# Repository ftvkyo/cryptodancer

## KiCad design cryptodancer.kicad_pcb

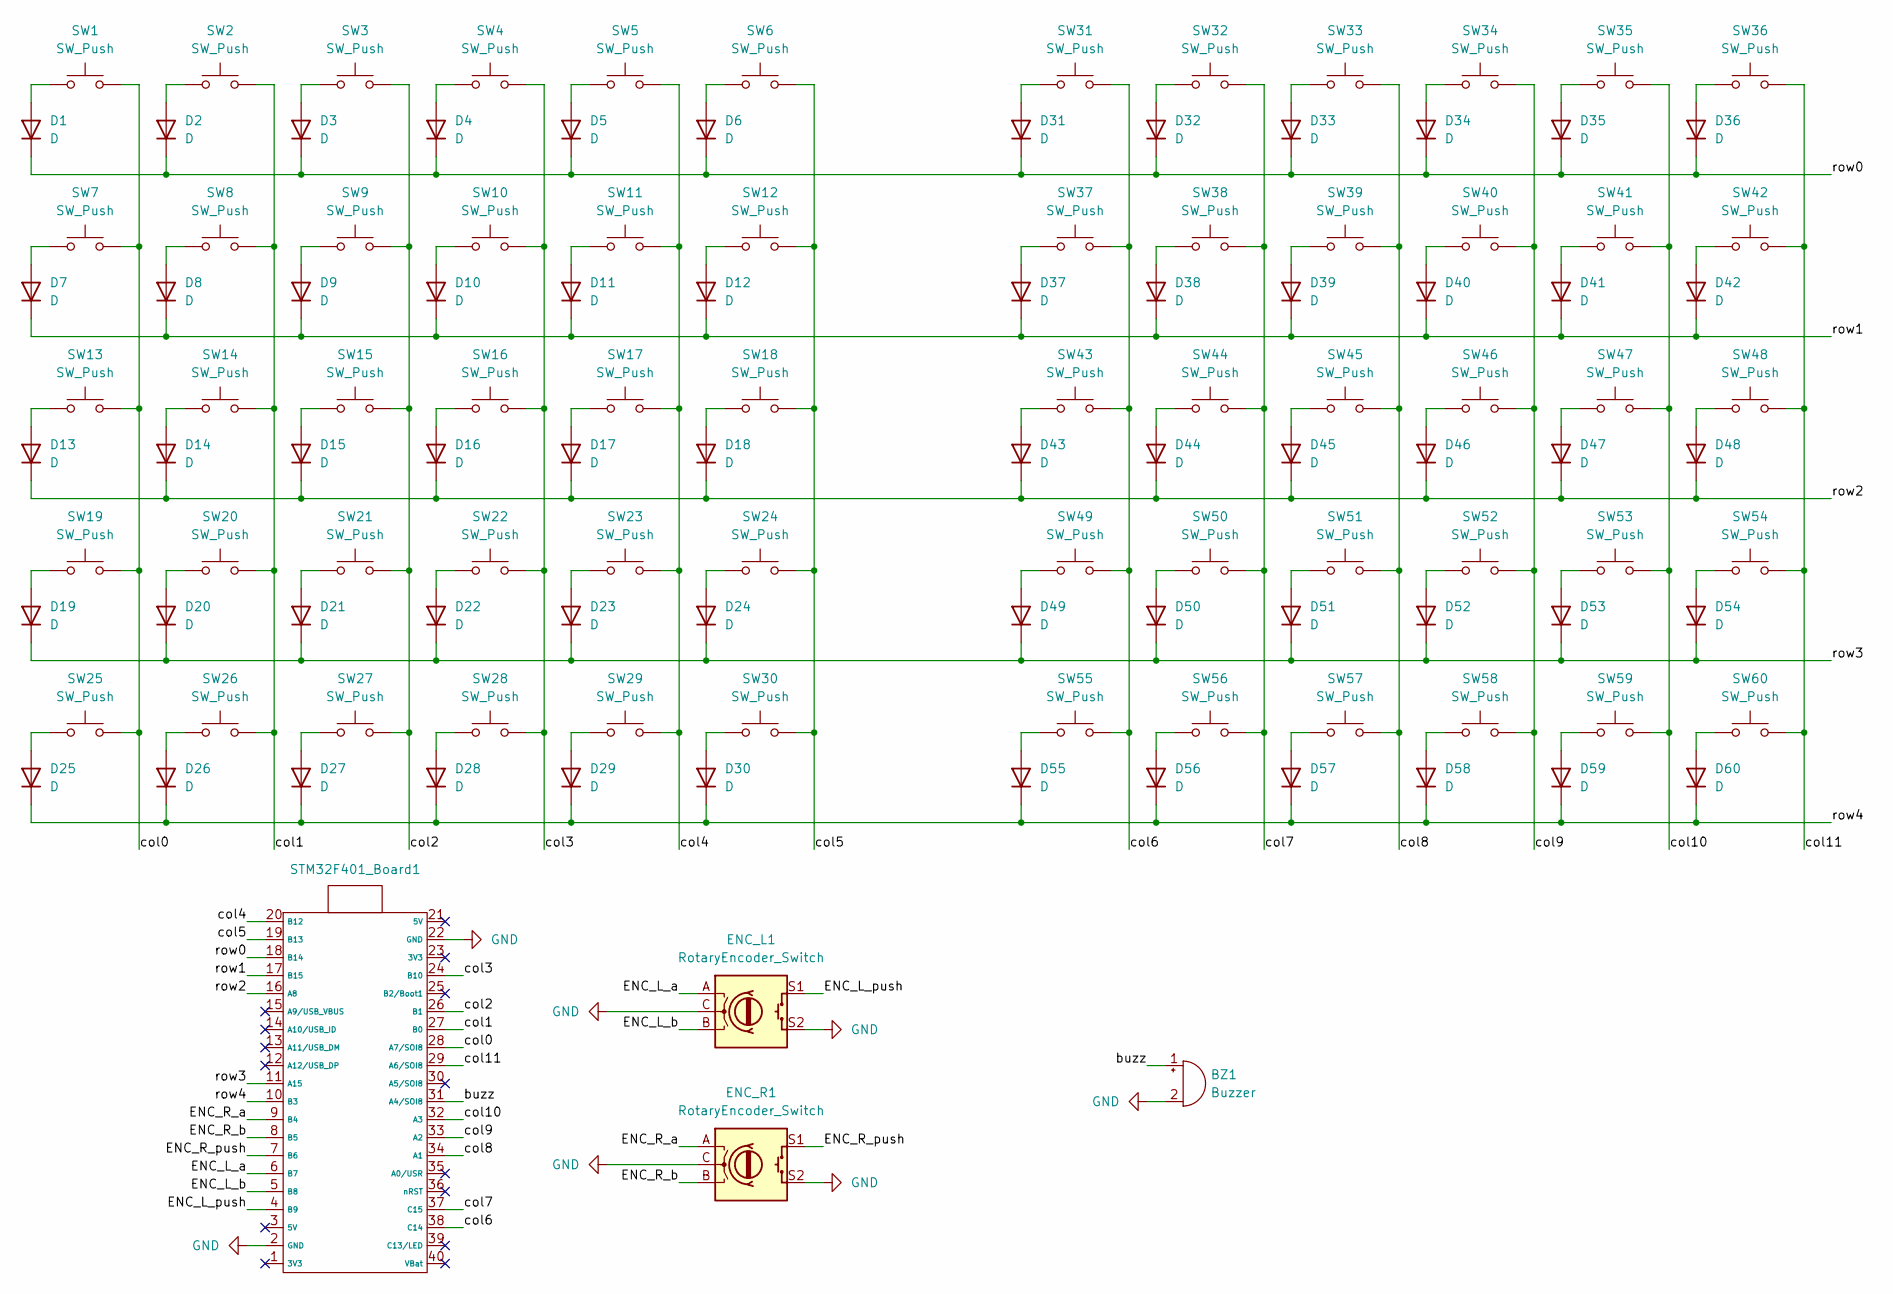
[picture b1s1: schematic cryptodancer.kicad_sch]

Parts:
BZ1: Buzzer; Buzzer_Murata_PKLCS1212E
D1, D2, D3, D4, D5, D6, D7, D8, D9, D10, D11, D12, D13, D14, D15, D16, D17, D18, D19, D20, D21, D22, D23, D24, D25, D26, D27, D28, D29, D30, D31, D32, D33, D34, D35, D36, D37, D38, D39, D40, D41, D42, D43, D44, D45, D46, D47, D48, D49, D50, D51, D52, D53, D54, D55, D56, D57, D58, D59, D60: D; D_1N4148_TH
ENC_L1: RotaryEncoder_Switch; RotaryEncoder_Alps_EC11E-Switch_Vertical_H20mm_MountingHoles
ENC_R1: RotaryEncoder_Switch; RotaryEncoder_Alps_EC11E-Switch_Vertical_H20mm_MountingHoles
STM32F401_Board1: STM32F401_Board
SW1, SW2, SW3, SW4, SW5, SW6, SW7, SW8, SW9, SW10, SW11, SW12, SW13, SW14, SW15, SW16, SW17, SW18, SW19, SW20, SW21, SW22, SW23, SW24, SW25, SW26, SW27, SW28, SW29, SW30, SW31, SW32, SW33, SW34, SW35, SW36, SW37, SW38, SW39, SW40, SW41, SW42, SW43, SW44, SW45, SW46, SW47, SW48, SW49, SW50, SW51, SW52, SW53, SW54, SW55, SW56, SW57, SW58, SW59, SW60: SW_Push; Kailh Choc v1 socket with switch

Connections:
/ENC_L_a: ENC_L1.A, STM32F401_Board1.6 (B7)
/ENC_L_b: ENC_L1.B, STM32F401_Board1.5 (B8)
/ENC_L_push: ENC_L1.S1, STM32F401_Board1.4 (B9)
/ENC_R_a: ENC_R1.A, STM32F401_Board1.9 (B4)
/ENC_R_b: ENC_R1.B, STM32F401_Board1.8 (B5)
/ENC_R_push: ENC_R1.S1, STM32F401_Board1.7 (B6)
/buzz: BZ1.1 (+), STM32F401_Board1.31 (A4/SOI8)
/col0: STM32F401_Board1.28 (A7/SOI8), SW1.2, SW7.2, SW13.2, SW19.2, SW25.2
/col1: STM32F401_Board1.27 (B0), SW2.2, SW8.2, SW14.2, SW20.2, SW26.2
/col2: STM32F401_Board1.26 (B1), SW3.2, SW9.2, SW15.2, SW21.2, SW27.2
/col3: STM32F401_Board1.24 (B10), SW4.2, SW10.2, SW16.2, SW22.2, SW28.2
/col4: STM32F401_Board1.20 (B12), SW5.2, SW11.2, SW17.2, SW23.2, SW29.2
/col5: STM32F401_Board1.19 (B13), SW6.2, SW12.2, SW18.2, SW24.2, SW30.2
/col6: STM32F401_Board1.38 (C14), SW31.2, SW37.2, SW43.2, SW49.2, SW55.2
/col7: STM32F401_Board1.37 (C15), SW32.2, SW38.2, SW44.2, SW50.2, SW56.2
/col8: STM32F401_Board1.34 (A1), SW33.2, SW39.2, SW45.2, SW51.2, SW57.2
/col9: STM32F401_Board1.33 (A2), SW34.2, SW40.2, SW46.2, SW52.2, SW58.2
/col10: STM32F401_Board1.32 (A3), SW35.2, SW41.2, SW47.2, SW53.2, SW59.2
/col11: STM32F401_Board1.29 (A6/SOI8), SW36.2, SW42.2, SW48.2, SW54.2, SW60.2
/row0: D1.1 (K), D2.1 (K), D3.1 (K), D4.1 (K), D5.1 (K), D6.1 (K), D31.1 (K), D32.1 (K), D33.1 (K), D34.1 (K), D35.1 (K), D36.1 (K), STM32F401_Board1.18 (B14)
/row1: D7.1 (K), D8.1 (K), D9.1 (K), D10.1 (K), D11.1 (K), D12.1 (K), D37.1 (K), D38.1 (K), D39.1 (K), D40.1 (K), D41.1 (K), D42.1 (K), STM32F401_Board1.17 (B15)
/row2: D13.1 (K), D14.1 (K), D15.1 (K), D16.1 (K), D17.1 (K), D18.1 (K), D43.1 (K), D44.1 (K), D45.1 (K), D46.1 (K), D47.1 (K), D48.1 (K), STM32F401_Board1.16 (A8)
/row3: D19.1 (K), D20.1 (K), D21.1 (K), D22.1 (K), D23.1 (K), D24.1 (K), D49.1 (K), D50.1 (K), D51.1 (K), D52.1 (K), D53.1 (K), D54.1 (K), STM32F401_Board1.11 (A15)
/row4: D25.1 (K), D26.1 (K), D27.1 (K), D28.1 (K), D29.1 (K), D30.1 (K), D55.1 (K), D56.1 (K), D57.1 (K), D58.1 (K), D59.1 (K), D60.1 (K), STM32F401_Board1.10 (B3)
GND: BZ1.2 (-), ENC_L1.C, ENC_L1.S2, ENC_R1.C, ENC_R1.S2, STM32F401_Board1.2 (GND), STM32F401_Board1.22 (GND)
unnamed: D1.2 (A), SW1.1
unnamed: D2.2 (A), SW2.1
unnamed: D3.2 (A), SW3.1
unnamed: D4.2 (A), SW4.1
unnamed: D5.2 (A), SW5.1
unnamed: D6.2 (A), SW6.1
unnamed: D7.2 (A), SW7.1
unnamed: D8.2 (A), SW8.1
unnamed: D9.2 (A), SW9.1
unnamed: D10.2 (A), SW10.1
unnamed: D11.2 (A), SW11.1
unnamed: D12.2 (A), SW12.1
unnamed: D13.2 (A), SW13.1
unnamed: D14.2 (A), SW14.1
unnamed: D15.2 (A), SW15.1
unnamed: D16.2 (A), SW16.1
unnamed: D17.2 (A), SW17.1
unnamed: D18.2 (A), SW18.1
unnamed: D19.2 (A), SW19.1
unnamed: D20.2 (A), SW20.1
unnamed: D21.2 (A), SW21.1
unnamed: D22.2 (A), SW22.1
unnamed: D23.2 (A), SW23.1
unnamed: D24.2 (A), SW24.1
unnamed: D25.2 (A), SW25.1
unnamed: D26.2 (A), SW26.1
unnamed: D27.2 (A), SW27.1
unnamed: D28.2 (A), SW28.1
unnamed: D29.2 (A), SW29.1
unnamed: D30.2 (A), SW30.1
unnamed: D31.2 (A), SW31.1
unnamed: D32.2 (A), SW32.1
unnamed: D33.2 (A), SW33.1
unnamed: D34.2 (A), SW34.1
unnamed: D35.2 (A), SW35.1
unnamed: D36.2 (A), SW36.1
unnamed: D37.2 (A), SW37.1
unnamed: D38.2 (A), SW38.1
unnamed: D39.2 (A), SW39.1
unnamed: D40.2 (A), SW40.1
unnamed: D41.2 (A), SW41.1
unnamed: D42.2 (A), SW42.1
unnamed: D43.2 (A), SW43.1
unnamed: D44.2 (A), SW44.1
unnamed: D45.2 (A), SW45.1
unnamed: D46.2 (A), SW46.1
unnamed: D47.2 (A), SW47.1
unnamed: D48.2 (A), SW48.1
unnamed: D49.2 (A), SW49.1
unnamed: D50.2 (A), SW50.1
unnamed: D51.2 (A), SW51.1
unnamed: D52.2 (A), SW52.1
unnamed: D53.2 (A), SW53.1
unnamed: D54.2 (A), SW54.1
unnamed: D55.2 (A), SW55.1
unnamed: D56.2 (A), SW56.1
unnamed: D57.2 (A), SW57.1
unnamed: D58.2 (A), SW58.1
unnamed: D59.2 (A), SW59.1
unnamed: D60.2 (A), SW60.1

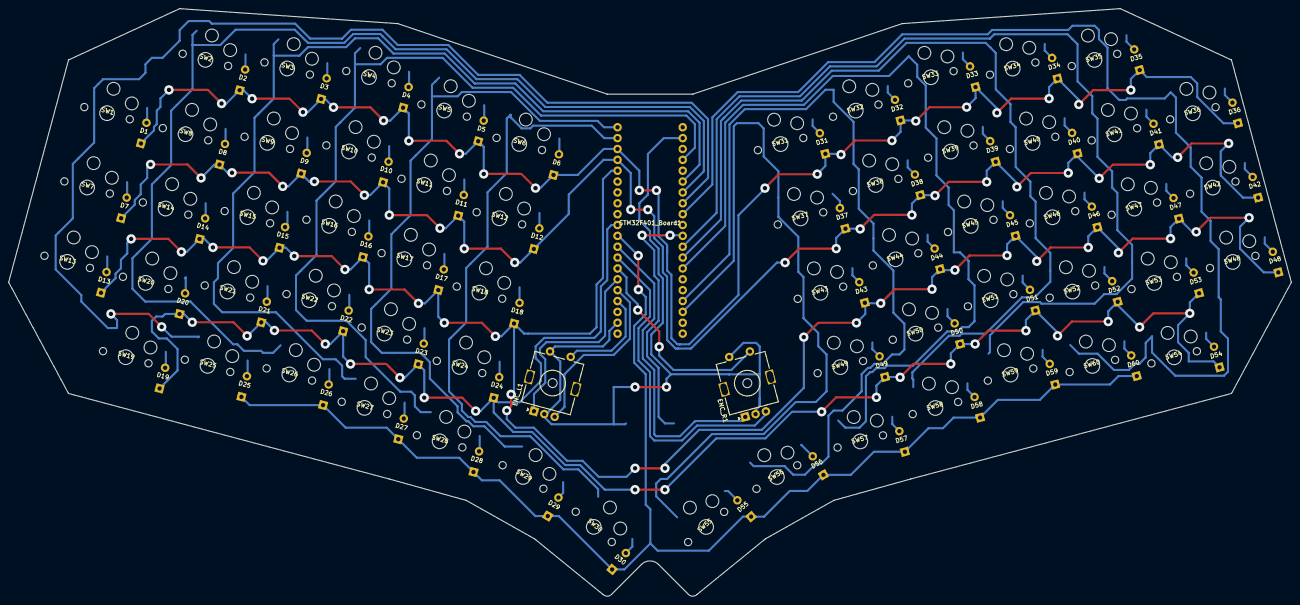
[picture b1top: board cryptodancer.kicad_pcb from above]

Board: 2 copper layers, 300.0 x 137.4 mm, 124 parts (1 on the bottom side), 85 nets.

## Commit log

2025-02-26 initial wiring
2025-02-26 neat wiring
2025-02-26 add simple edge cuts
2025-02-27 reduce width to fit in 300mm
2025-02-27 reroute using a better diode footprint and updated via sizes
2025-03-19 move the PCB to be in positive coordinates
2025-03-19 rename to cryptodancer
2025-03-19 Add exported SVGs and a fab file for ftvkyo/svg2gcode
2025-03-22 ignore #auto_saved_files#
2025-03-22 use pin A4 for the buzzer
2025-03-22 add a milling pass for encoder legs
2025-03-23 fix buzzer trace
2025-06-17 Convert fab config from YAML to TOML
